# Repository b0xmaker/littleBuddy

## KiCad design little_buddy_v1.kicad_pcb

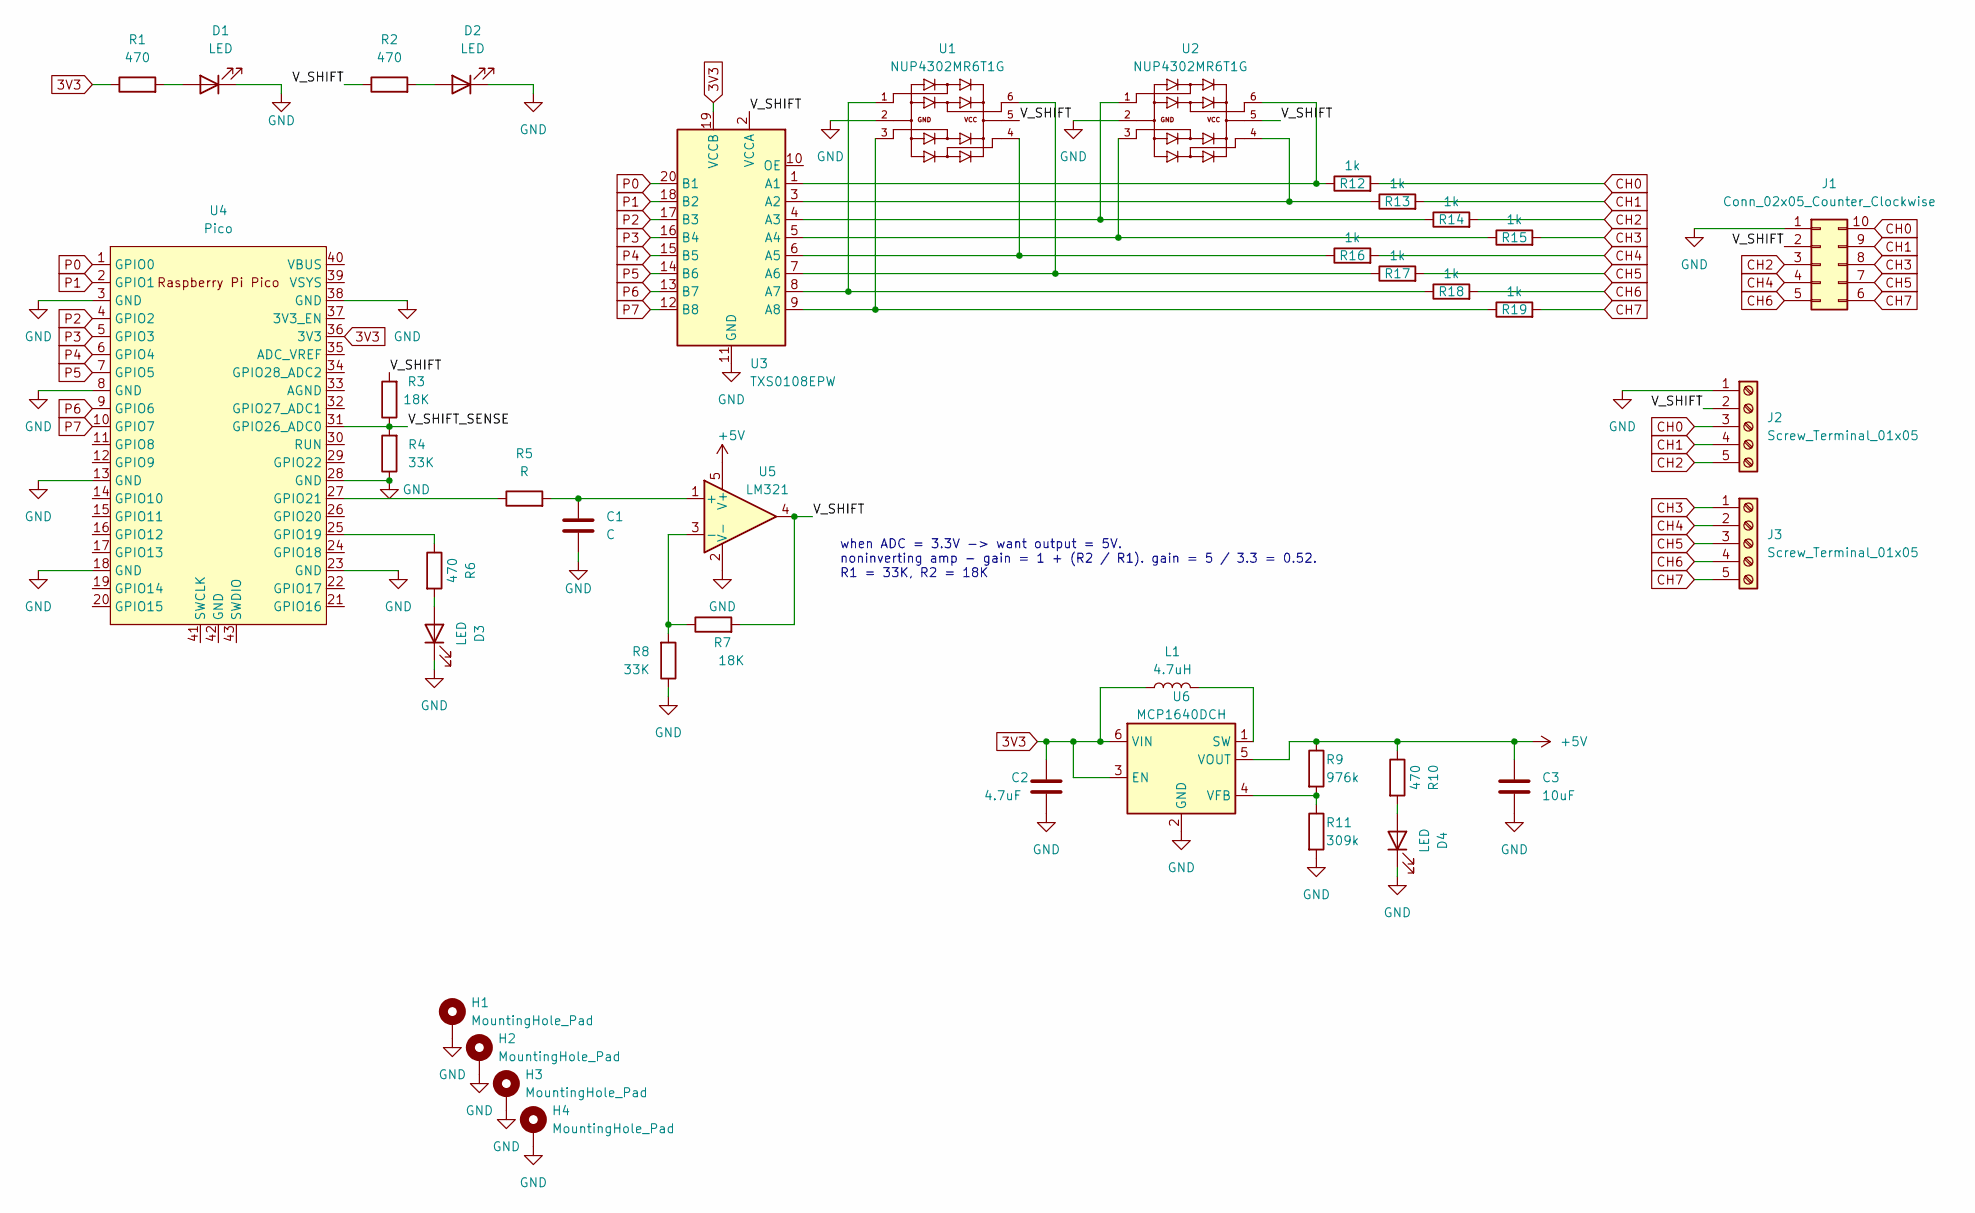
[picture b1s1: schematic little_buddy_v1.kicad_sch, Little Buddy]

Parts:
C1: C; C_0805_2012Metric_Pad1.18x1.45mm_HandSolder
C2: 4.7uF; C_0805_2012Metric_Pad1.18x1.45mm_HandSolder
C3: 10uF; C_0805_2012Metric_Pad1.18x1.45mm_HandSolder
D1, D2, D3, D4: LED; LED_0805_2012Metric_Pad1.15x1.40mm_HandSolder
H1, H2, H3, H4: MountingHole_Pad; MountingHole_2.7mm_Pad_Via
J1: Conn_02x05_Counter_Clockwise; THT+SMD
J2, J3: Screw_Terminal_01x05; TerminalBlock_Phoenix_MKDS-1,5-5_1x05_P5.00mm_Horizontal
L1: 4.7uH; L_0805_2012Metric_Pad1.15x1.40mm_HandSolder
R1, R2, R6, R10: 470; R_0805_2012Metric_Pad1.20x1.40mm_HandSolder
R3, R7: 18K; R_0805_2012Metric_Pad1.20x1.40mm_HandSolder
R4, R8: 33K; R_0805_2012Metric_Pad1.20x1.40mm_HandSolder
R5: R; R_0805_2012Metric_Pad1.20x1.40mm_HandSolder
R9: 976k; R_0805_2012Metric_Pad1.20x1.40mm_HandSolder
R11: 309k; R_0805_2012Metric_Pad1.20x1.40mm_HandSolder
R12, R13, R14, R15, R16, R17, R18, R19: 1k; R_0805_2012Metric_Pad1.20x1.40mm_HandSolder
U1, U2: NUP4302MR6T1G; TSOP-6_1.65x3.05mm_P0.95mm; PARTREV 12 JUN 2012
U3: TXS0108EPW; TSSOP-20_4.4x6.5mm_P0.65mm
U4: Pico; RPi_Pico_SMD_TH
U5: LM321; SOT-23-5
U6: MCP1640DCH; SOT-23-6

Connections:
3V3: C2.1, L1.1, R1.1, U3.19 (VCCB), U4.36 (3V3), U6.3 (EN), U6.6 (VIN)
+5V: C3.1, R9.1, R10.1, U5.5 (V+), U6.5 (VOUT)
/V_SHIFT: J1.2, J2.2, R2.1, R3.2, R7.2, U1.5, U2.5, U3.2 (VCCA), U5.4
/V_SHIFT_SENSE: R3.1, R4.2, U4.31 (GPIO26_ADC0)
CH0: J1.10, J2.3, R12.2
CH1: J1.9, J2.4, R13.2
CH2: J1.3, J2.5, R14.2
CH3: J1.8, J3.1, R15.2
CH4: J1.4, J3.2, R16.2
CH5: J1.7, J3.3, R17.2
CH6: J1.5, J3.4, R18.2
CH7: J1.6, J3.5, R19.2
GND: C1.1, C2.2, C3.2, D1.1 (K), D2.1 (K), D3.1 (K), D4.1 (K), H1.1, H2.1, H3.1, H4.1, J1.1, J2.1, R4.1, R8.1, R11.2, U1.2, U2.2, U3.11 (GND), U4.3 (GND), U4.8 (GND), U4.13 (GND), U4.18 (GND), U4.23 (GND), U4.28 (GND), U4.38 (GND), U5.2 (V-), U6.2 (GND)
unnamed: D1.2 (A), R1.2
unnamed: D2.2 (A), R2.2
unnamed: D3.2 (A), R6.2
unnamed: D4.2 (A), R10.2
unnamed: R12.1, U2.6, U3.1 (A1)
unnamed: R13.1, U2.4, U3.3 (A2)
unnamed: R14.1, U2.1, U3.4 (A3)
unnamed: R15.1, U2.3, U3.5 (A4)
unnamed: R16.1, U1.4, U3.6 (A5)
unnamed: R17.1, U1.6, U3.7 (A6)
unnamed: R18.1, U1.1, U3.8 (A7)
unnamed: R19.1, U1.3, U3.9 (A8)
unnamed: R6.1, U4.25 (GPIO19)
unnamed: R5.1, U4.27 (GPIO21)
unnamed: C1.2, R5.2, U5.1 (+)
unnamed: R7.1, R8.2, U5.3 (-)
unnamed: L1.2, U6.1 (SW)
unnamed: R9.2, R11.1, U6.4 (VFB)
P0: U3.20 (B1), U4.1 (GPIO0)
P1: U3.18 (B2), U4.2 (GPIO1)
P2: U3.17 (B3), U4.4 (GPIO2)
P3: U3.16 (B4), U4.5 (GPIO3)
P4: U3.15 (B5), U4.6 (GPIO4)
P5: U3.14 (B6), U4.7 (GPIO5)
P6: U3.13 (B7), U4.9 (GPIO6)
P7: U3.12 (B8), U4.10 (GPIO7)

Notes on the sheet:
when ADC = 3.3V -> want output = 5V. noninverting amp - gain = 1 + (R2 / R1). gain = 5 / 3.3 = 0.52. R1 = 33K, R2 = 18K

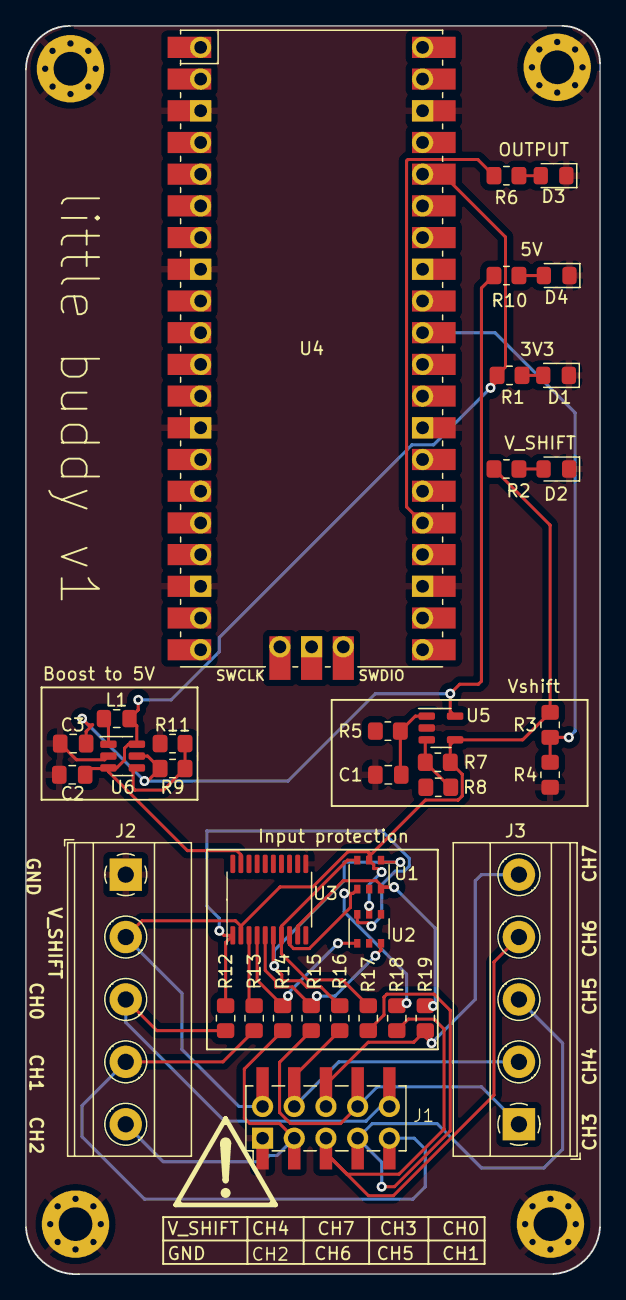
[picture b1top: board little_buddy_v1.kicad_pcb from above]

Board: 2 copper layers, 46.0 x 100.0 mm, 40 parts (0 on the bottom side), 39 nets.
